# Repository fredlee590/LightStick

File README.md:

# LightStick

A short stick with LEDs and an IMU in it. Modulate, change color, etc based on movement. Should be a good show.

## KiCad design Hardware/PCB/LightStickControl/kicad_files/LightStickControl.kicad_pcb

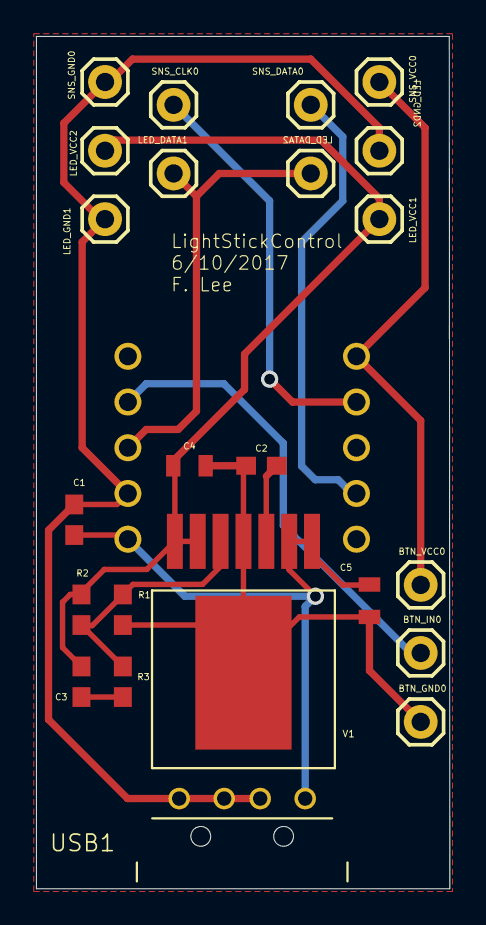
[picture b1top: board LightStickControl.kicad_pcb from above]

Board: 2 copper layers, 23.0 x 47.3 mm, 24 parts (1 on the bottom side), 11 nets.

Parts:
BTN_GND0: 1X01
BTN_IN0: 1X01
BTN_VCC0: 1X01
C1: 4.7uF; 0603
C2: 10nF; 0603
C3: 100pF; 0603
C4: 47uF; 0805
C5: 22uF; 0805
LED_DATA1, LED_DATA2: 1X01
LED_GND1, LED_GND2: 1X01
LED_VCC1, LED_VCC2: 1X01
MCU1: ARDUINO_TRINKET
R1: 33k; 0603
R2: 100k; 0603
R3: 4.53k; 0603
SNS_CLK0: 1X01
SNS_DATA0: 1X01
SNS_GND0: 1X01
SNS_VCC0: 1X01
USB1: USB_A_932
V1: LMZ10503; TO-PMOD

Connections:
BTN_IN: BTN_IN0.1, MCU1.PB3
FB: R1.2, R2.1, R3.2, V1.FB
GND: BTN_GND0.1, C1.2, C2.1, C4.2, C5.2, LED_GND1.1, LED_GND2.1, MCU1.GND, R1.1, SNS_GND0.1, USB1.D+, USB1.D-, USB1.GND, V1.GND, V1.GND_PAD
LED_DATA: LED_DATA1.1, LED_DATA2.1, MCU1.PB4
SNS_CLK: MCU1.PB2, SNS_CLK0.1
SNS_DATA: MCU1.PB0, SNS_DATA0.1
SNS_VCC: BTN_VCC0.1, MCU1.3.3V, SNS_VCC0.1
SS: C2.2, V1.SS
VCC_IN: C1.1, C5.1, MCU1.BATT, USB1.VCC, V1.EN, V1.VIN
VOUT: C3.2, C4.1, LED_VCC1.1, LED_VCC2.1, R2.2, V1.VOUT1, V1.VOUT2
VOUT_C: C3.1, R3.1

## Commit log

2017-03-08 Initial check in of LightStick project. Move to new format of Github.
2017-03-08 First cut of board layout. Add connectors. Label everything.
2017-03-09 Add support components and lay initial placement.
2017-03-09 Added routing.
2017-04-12 Shorten PCB to allow for a snug fit for the USB plug A
2017-04-17 Add 3D printed parts to maintain circuit board cohesion.
2017-04-19 Rebuild Tip Cap.
2017-04-19 Add folder for accelerometer PCB
2017-04-20 Planning for physical build out of the Light Stick blade and accelerometer circuit.
2017-04-20 Move LightStick blade from PCB directory to Laser cutting directory.
2017-04-25 Add rainbow fade for light stick
2017-04-28 Add LightStickAccelerometer schematic and board. Update eagle project file accordingly.
2017-04-28 Add slot for PCB
2017-04-28 Adjust PCB bounds.
2017-04-29 Move components to allow for some empty space on top and bottom.
2017-04-29 Use Laen's design rules in design rule check.
2017-05-08 Rename LaserCutting to reflect ends rather than means.
2017-05-08 Create directory for LightStickButtonPCB. Start with datasheet.
2017-05-08 Plan out Light stick button PCB.
2017-05-10 Create PCB for LightStick button.
2017-05-23 LightStickButton fixes. Holes moved to proper mirrored places. Through-holes widened.
2017-06-12 Add new switching voltage regulator.
2017-06-12 Add ground plane to top layer.
2017-06-29 Initial check in of accelerometer proof of concept. Can use it in lightweight manner. Add todo.
2019-10-14 Initial check in of basic Light Stick sketch
    Initial check in of simplest Light Stick sketch to use accelerometer in
    color determination.
2023-12-28 Import to KiCad
    Convert Eagle files into KiCad files for further development.
